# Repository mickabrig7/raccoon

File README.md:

# 🦝 raccoon
The open-source car bus analyzer !

A raccoon is a trash [panda](https://comma.ai/shop/products/panda), literally.

Instructions coming **soon™**

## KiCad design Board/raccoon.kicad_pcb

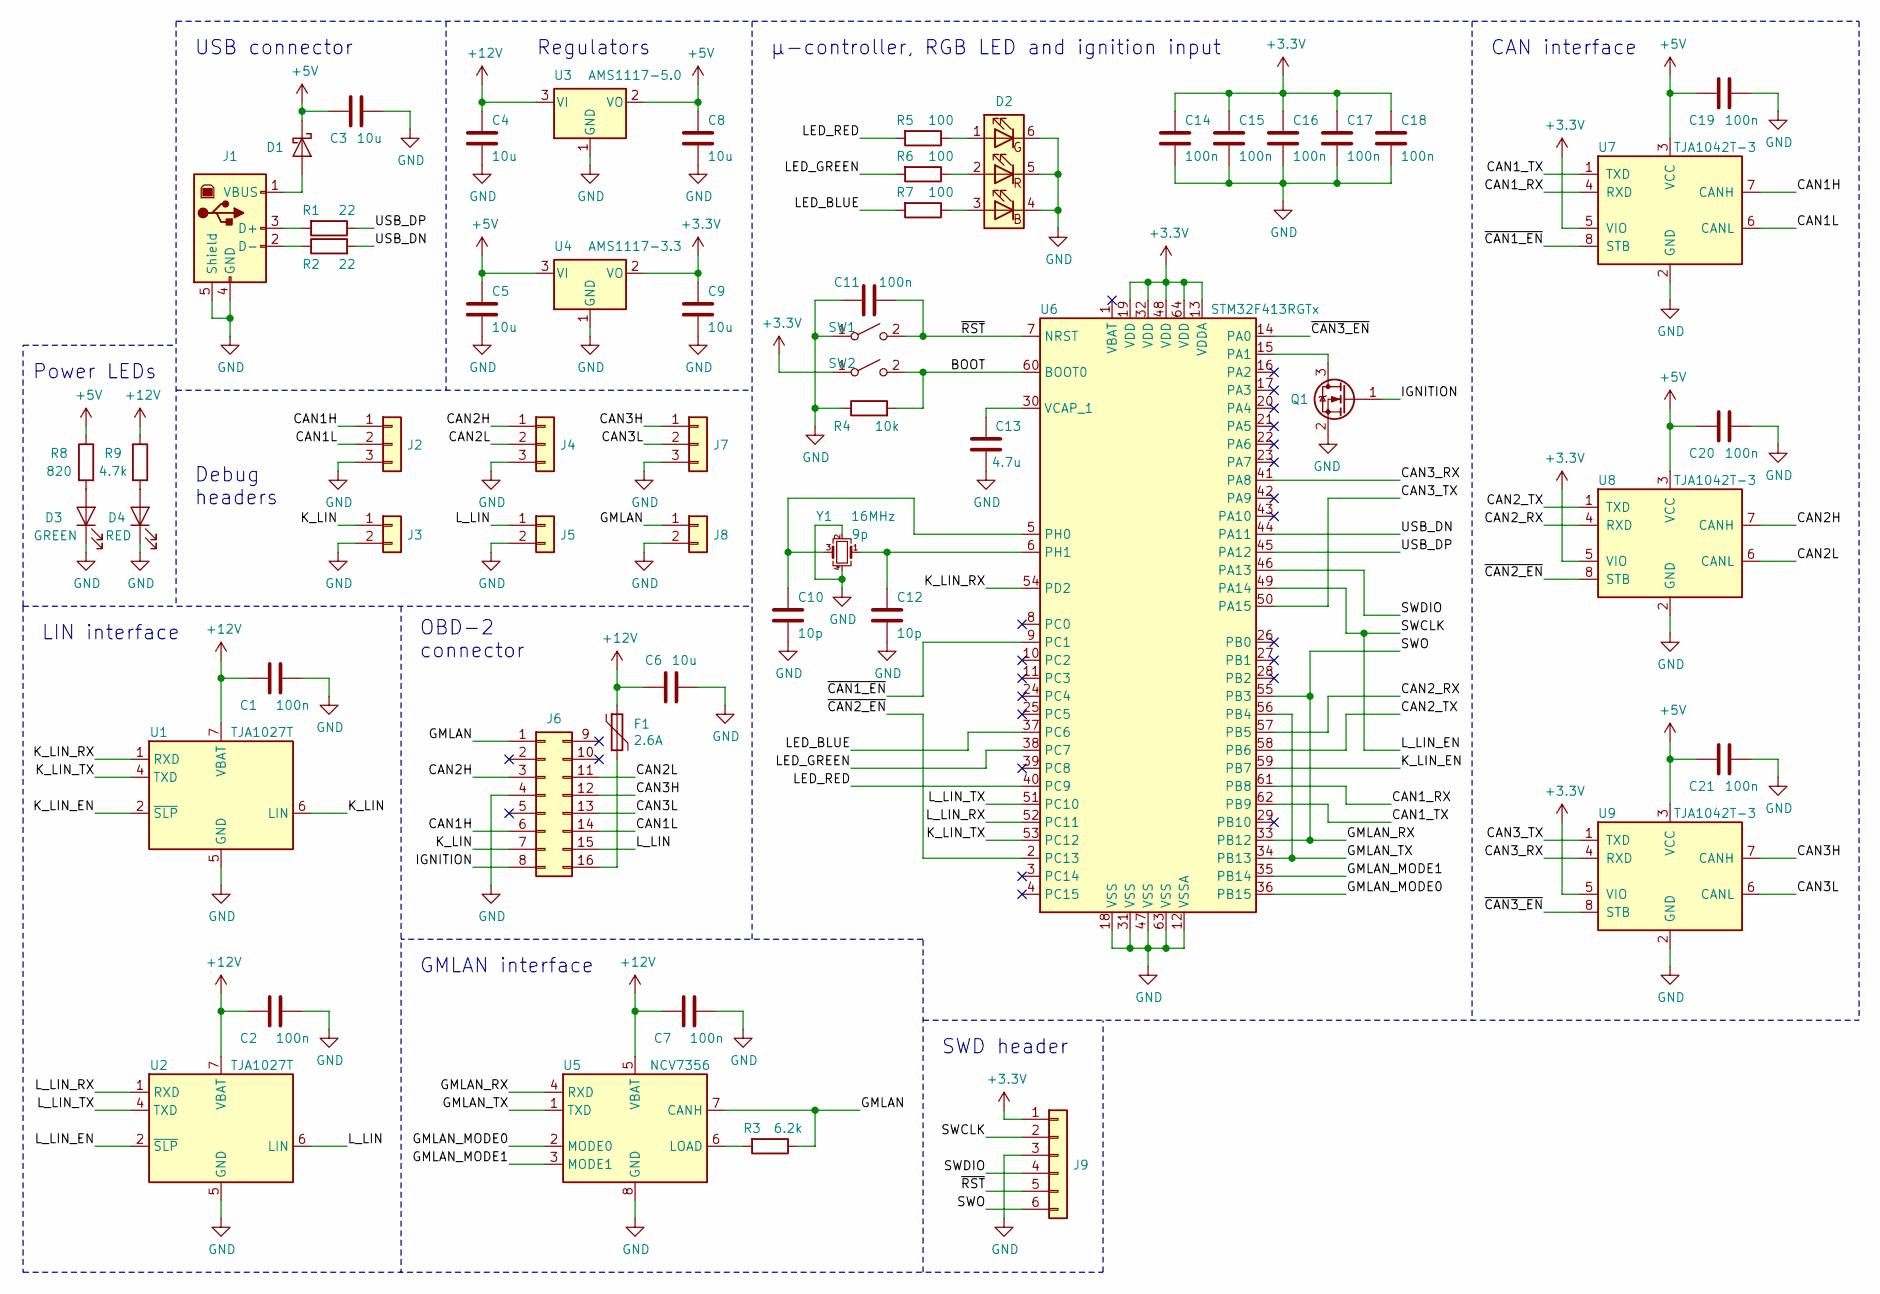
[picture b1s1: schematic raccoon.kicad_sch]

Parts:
C1, C2, C7, C11, C14, C15, C16, C17, C18, C19, C20, C21: 100n; C_0603_1608Metric; LCSC C14663
C3, C4, C5, C6, C8, C9: 10u; C_0805_2012Metric; LCSC C15850
C10, C12: 10p; C_0402_1005Metric; LCSC C32949
C13: 4.7u; C_0603_1608Metric; LCSC C19666
D1: D_Schottky; D_SMA; LCSC C8678
D2: LED_RGB; LED_RGB_5050-6
D3: GREEN; LED_0603_1608Metric_Castellated; LCSC C72043
D4: RED; LED_0603_1608Metric_Castellated; LCSC C2286
F1: 2.6A; Fuse_1812_4532Metric
J1: USB_B; USB_B_OST_USB-B1HSxx_Horizontal
J2, J4, J7: Conn_01x03; PinHeader_1x03_P2.54mm_Vertical
J3, J5, J8: Conn_01x02; PinHeader_1x02_P2.54mm_Vertical
J6: Conn_02x08_Top_Bottom; IDC-Header_2x08_P2.54mm_Vertical
J9: Conn_01x06; PinHeader_1x06_P2.54mm_Vertical
Q1: Q_NMOS_GSD; SOT-23; LCSC C8545
R1, R2: 22; R_0603_1608Metric; LCSC C23345
R3: 6.2k; R_0603_1608Metric; LCSC C4260
R4: 10k; R_0603_1608Metric; LCSC C25804
R5, R6, R7: 100; R_0603_1608Metric; LCSC C22775
R8: 820; R_0603_1608Metric; LCSC C23253
R9: 4.7k; R_0603_1608Metric; LCSC C23162
SW1, SW2: SW_SPST; SW_PUSH_6mm_H8mm
U1, U2: TJA1027T; SOIC-8_3.9x4.9mm_P1.27mm
U3: AMS1117-5.0; SOT-223-3_TabPin2; LCSC C6187
U4: AMS1117-3.3; SOT-223-3_TabPin2; LCSC C6186
U5: NCV7356; SOIC-8_3.9x4.9mm_P1.27mm
U6: STM32F413RGTx; LQFP-64_10x10mm_P0.5mm
U7, U8, U9: TJA1042T-3; SOIC-8_3.9x4.9mm_P1.27mm
Y1: 16MHz; Crystal_SMD_3225-4Pin_3.2x2.5mm; LCSC C13738

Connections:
+3V3: C9.1, C14.1, C15.1, C16.1, C17.1, C18.1, J9.1, SW2.1 (A), U4.2 (VO), U6.13 (VDDA), U6.19 (VDD), U6.32 (VDD), U6.48 (VDD), U6.64 (VDD), U7.5 (VIO), U8.5 (VIO), U9.5 (VIO)
+5V: C3.2, C5.1, C8.1, C19.2, C20.2, C21.2, D1.1 (K), R8.1, U3.2 (VO), U4.3 (VI), U7.3 (VCC), U8.3 (VCC), U9.3 (VCC)
+12V: C1.2, C2.2, C4.1, C6.2, C7.2, F1.1, R9.1, U1.7 (VBAT), U2.7 (VBAT), U3.3 (VI), U5.5 (VBAT)
/BOOT: R4.2, SW2.2 (B), U6.60 (BOOT0)
/CAN1H: J2.1, J6.6, U7.7 (CANH)
/CAN1L: J2.2, J6.14, U7.6 (CANL)
/CAN1_RX: U6.61 (PB8), U7.4 (RXD)
/CAN1_TX: U6.62 (PB9), U7.1 (TXD)
/CAN2H: J4.1, J6.3, U8.7 (CANH)
/CAN2L: J4.2, J6.11, U8.6 (CANL)
/CAN2_RX: U6.57 (PB5), U8.4 (RXD)
/CAN2_TX: U6.58 (PB6), U8.1 (TXD)
/CAN3H: J6.12, J7.1, U9.7 (CANH)
/CAN3L: J6.13, J7.2, U9.6 (CANL)
/CAN3_RX: U6.41 (PA8), U9.4 (RXD)
/CAN3_TX: U6.50 (PA15), U9.1 (TXD)
/GMLAN: J6.1, J8.1, R3.1, U5.7 (CANH)
/GMLAN_MODE0: U5.2 (MODE0), U6.36 (PB15)
/GMLAN_MODE1: U5.3 (MODE1), U6.35 (PB14)
/GMLAN_RX: J9.6, U5.4 (RXD), U6.33 (PB12), U6.55 (PB3)
/GMLAN_TX: U5.1 (TXD), U6.34 (PB13), U6.56 (PB4)
/IGNITION: J6.8, Q1.1 (G)
/K_LIN: J3.1, J6.7, U1.6 (LIN)
/K_LIN_EN: U1.2 (~SLP~), U6.59 (PB7)
/K_LIN_RX: U1.1 (RXD), U6.54 (PD2)
/K_LIN_TX: U1.4 (TXD), U6.53 (PC12)
/LED_BLUE: R7.2, U6.37 (PC6)
/LED_GREEN: R6.2, U6.38 (PC7)
/LED_RED: R5.2, U6.40 (PC9)
/L_LIN: J5.1, J6.15, U2.6 (LIN)
/L_LIN_EN: J9.2, U2.2 (~SLP~), U6.49 (PA14)
/L_LIN_RX: U2.1 (RXD), U6.52 (PC11)
/L_LIN_TX: U2.4 (TXD), U6.51 (PC10)
/SWDIO: J9.4, U6.46 (PA13)
/USB_DN: R2.2, U6.44 (PA11)
/USB_DP: R1.1, U6.45 (PA12)
/~CAN1_EN~: U6.9 (PC1), U7.8 (STB)
/~CAN2_EN~: U6.2 (PC13), U8.8 (STB)
/~CAN3_EN~: U6.14 (PA0), U9.8 (STB)
/~RST~: C11.1, J9.5, SW1.2 (B), U6.7 (NRST)
GND: C1.1, C2.1, C3.1, C4.2, C5.2, C6.1, C7.1, C8.2, C9.2, C10.2, C11.2, C12.2, C13.1, C14.2, C15.2, C16.2, C17.2, C18.2, C19.1, C20.1, C21.1, D2.4 (BK), D2.5 (GK), D2.6 (RK), D3.1 (K), D4.1 (K), J1.4 (GND), J1.5 (Shield), J2.3, J3.2, J4.3, J5.2, J6.4, J7.3, J8.2, J9.3, Q1.2 (S), R4.1, SW1.1 (A), U1.5 (GND), U2.5 (GND), U3.1 (GND), U4.1 (GND), U5.8 (GND), U6.12 (VSSA), U6.18 (VSS), U6.31 (VSS), U6.47 (VSS), U6.63 (VSS), U7.2 (GND), U8.2 (GND), U9.2 (GND), Y1.2, Y1.4
unnamed: C10.1, U6.5 (PH0), Y1.3
unnamed: C12.1, U6.6 (PH1), Y1.1
unnamed: C13.2, U6.30 (VCAP_1)
unnamed: D1.2 (A), J1.1 (VBUS)
unnamed: D2.1 (RA), R5.1
unnamed: D2.2 (GA), R6.1
unnamed: D2.3 (BA), R7.1
unnamed: D3.2 (A), R8.2
unnamed: D4.2 (A), R9.2
unnamed: F1.2, J6.16
unnamed: J1.2 (D-), R2.1
unnamed: J1.3 (D+), R1.2
unnamed: Q1.3 (D), U6.15 (PA1)
unnamed: R3.2, U5.6 (LOAD)

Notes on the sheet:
Power LEDs
LIN interface
USB connector
Debug headers
OBD-2 connector
GMLAN interface
Regulators
µ-controller, RGB LED and ignition input
SWD header
CAN interface

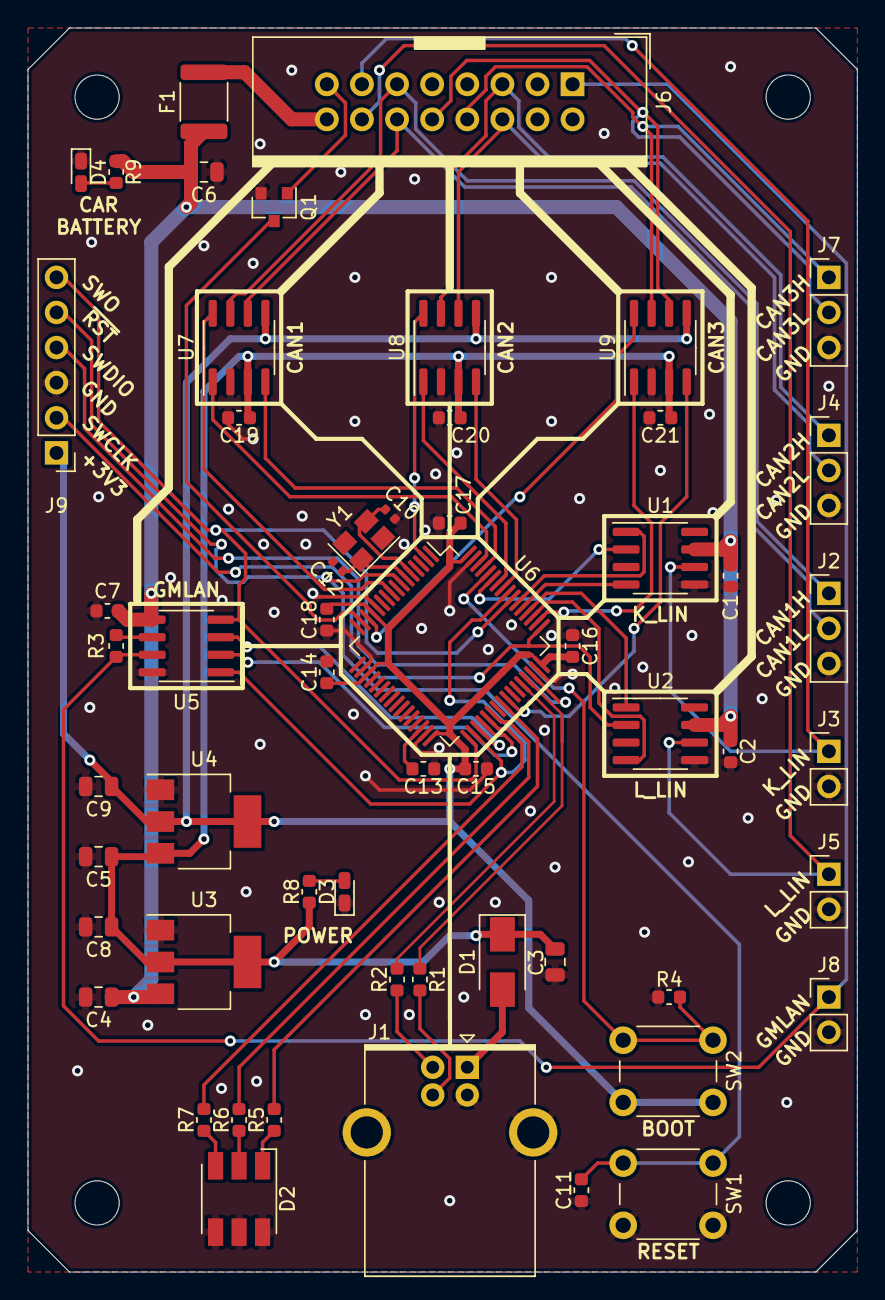
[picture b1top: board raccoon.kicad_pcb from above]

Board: 2 copper layers, 60.0 x 90.0 mm, 57 parts (0 on the bottom side), 55 nets.

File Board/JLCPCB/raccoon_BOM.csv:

Comment,Designator,Footprint,LCSC
"100n","C1,C2,C7,C11,C14,C15,C16,C17,C18,C19,C20,C21","Capacitor_SMD:C_0603_1608Metric","C14663"
"10p","C10,C12","Capacitor_SMD:C_0402_1005Metric","C32949"
"4.7u","C13","Capacitor_SMD:C_0603_1608Metric","C19666"
"10u","C3,C4,C5,C6,C8,C9","Capacitor_SMD:C_0805_2012Metric","C15850"
"D_Schottky","D1","Diode_SMD:D_SMA","C8678"
"LED_RGB","D2","LED_SMD:LED_RGB_5050-6",""
"GREEN","D3","LED_SMD:LED_0603_1608Metric_Castellated","C72043"
"RED","D4","LED_SMD:LED_0603_1608Metric_Castellated","C2286"
"2.6A","F1","Fuse:Fuse_1812_4532Metric",""
"USB_B","J1","Connector_USB:USB_B_OST_USB-B1HSxx_Horizontal",""
"Conn_01x03","J2,J4,J7","Connector_PinHeader_2.54mm:PinHeader_1x03_P2.54mm_Vertical",""
"Conn_01x02","J3,J5,J8","Connector_PinHeader_2.54mm:PinHeader_1x02_P2.54mm_Vertical",""
"Conn_02x08_Top_Bottom","J6","raccoon:IDC-Header_2x08_P2.54mm_Vertical",""
"Conn_01x06","J9","Connector_PinHeader_2.54mm:PinHeader_1x06_P2.54mm_Vertical",""
"Q_NMOS_GSD","Q1","Package_TO_SOT_SMD:SOT-23","C8545"
"22","R1,R2","Resistor_SMD:R_0603_1608Metric","C23345"
"6.2k","R3","Resistor_SMD:R_0603_1608Metric","C4260"
"10k","R4","Resistor_SMD:R_0603_1608Metric","C25804"
"100","R5,R6,R7","Resistor_SMD:R_0603_1608Metric","C22775"
"820","R8","Resistor_SMD:R_0603_1608Metric","C23253"
"4.7k","R9","Resistor_SMD:R_0603_1608Metric","C23162"
"SW_SPST","SW1,SW2","Button_Switch_THT:SW_PUSH_6mm_H8mm",""
"TJA1027T","U1,U2","Package_SO:SOIC-8_3.9x4.9mm_P1.27mm",""
"AMS1117-5.0","U3","Package_TO_SOT_SMD:SOT-223-3_TabPin2","C6187"
"AMS1117-3.3","U4","Package_TO_SOT_SMD:SOT-223-3_TabPin2","C6186"
"NCV7356","U5","Package_SO:SOIC-8_3.9x4.9mm_P1.27mm",""
"STM32F413RGTx","U6","Package_QFP:LQFP-64_10x10mm_P0.5mm",""
"TJA1042T-3","U7,U8,U9","Package_SO:SOIC-8_3.9x4.9mm_P1.27mm",""
"16MHz","Y1","Crystal:Crystal_SMD_3225-4Pin_3.2x2.5mm","C13738"

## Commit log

2021-05-25 Initial board commit
